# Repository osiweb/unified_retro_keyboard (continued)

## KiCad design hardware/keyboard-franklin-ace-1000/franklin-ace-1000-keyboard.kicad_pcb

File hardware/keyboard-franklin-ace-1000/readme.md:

# Franklin-ACE-1000-Keyboard
Replacement Franklin ACE 1000 keyboard for use with osiweb's Unified Retro Keyboard

## Images

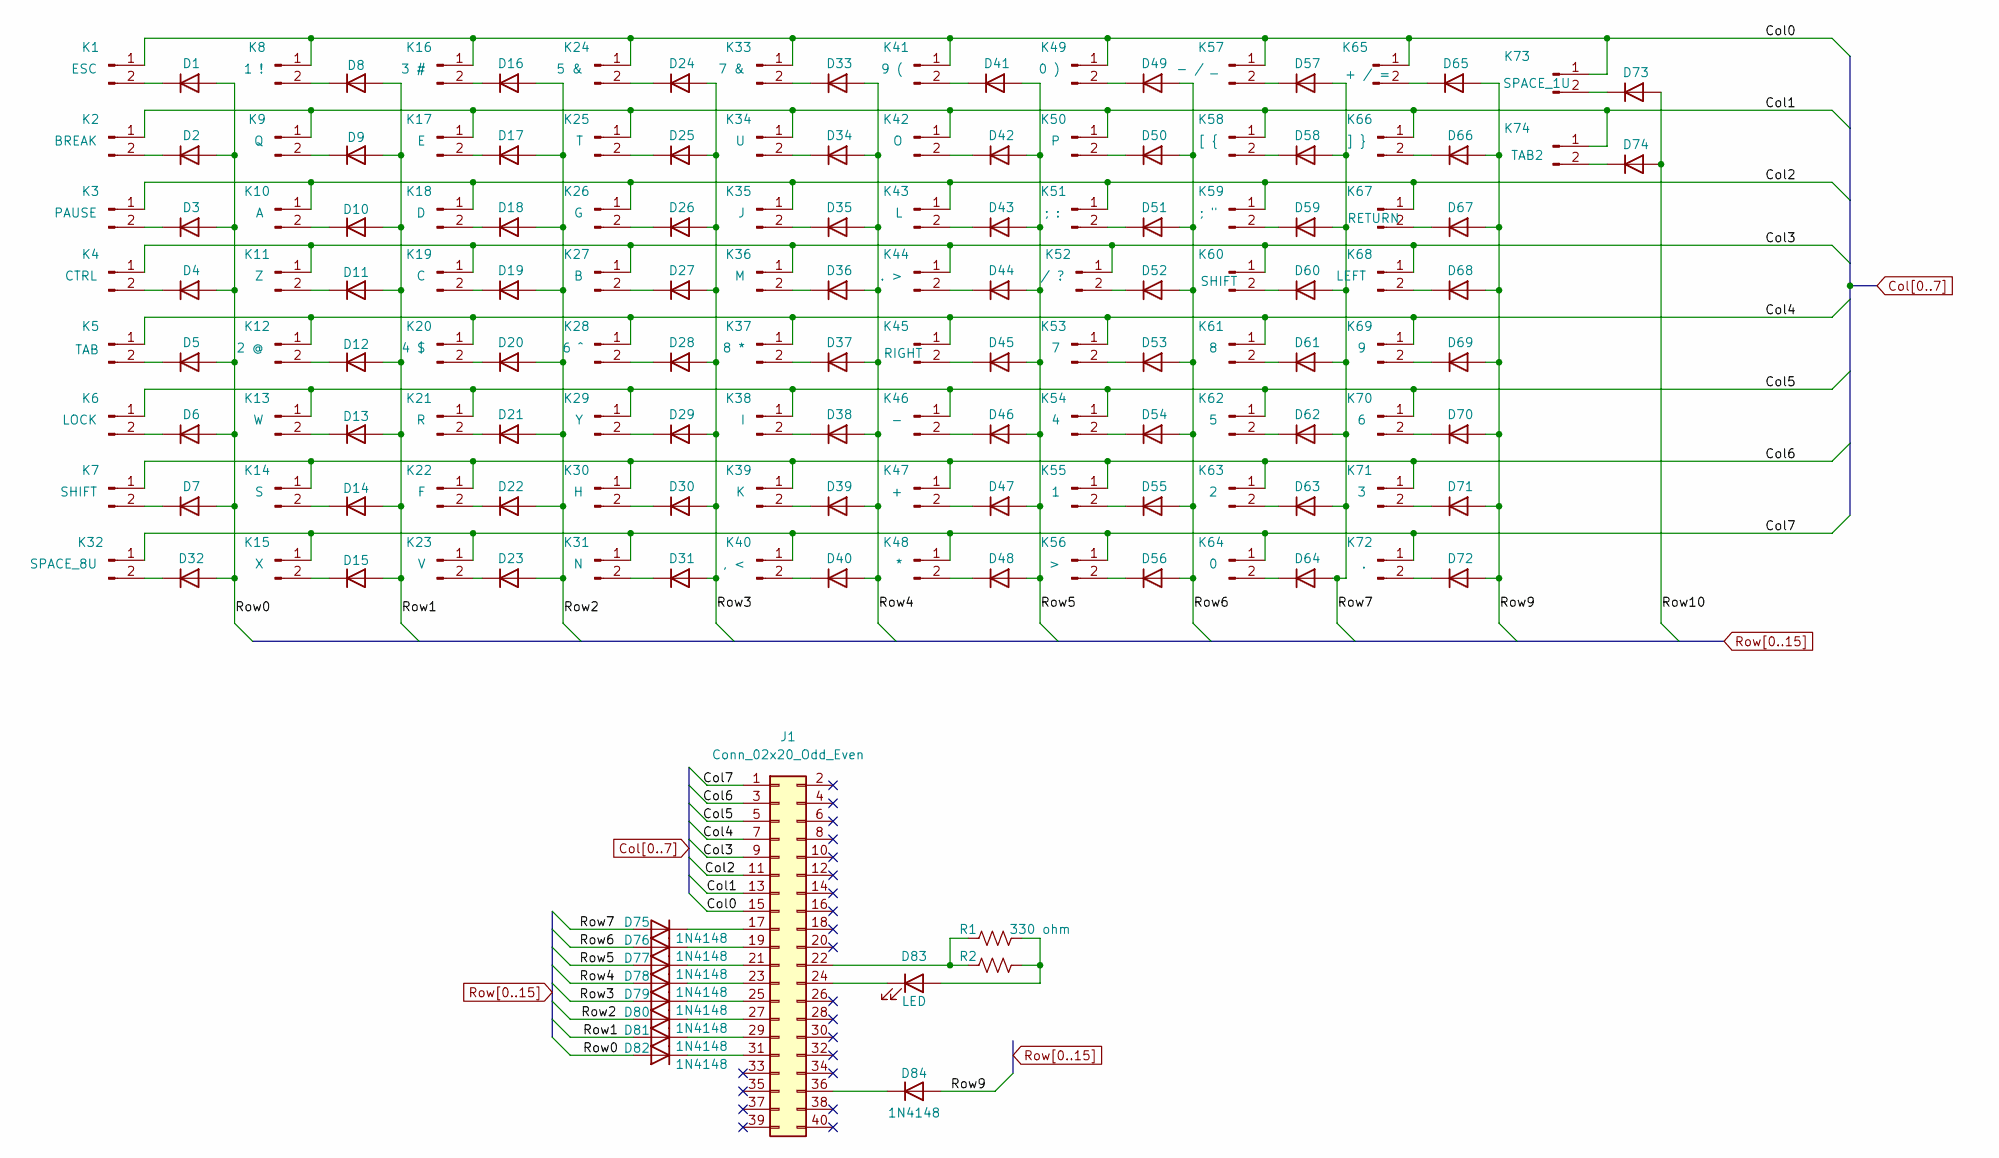
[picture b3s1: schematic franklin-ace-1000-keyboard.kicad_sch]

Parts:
D1, D2, D3, D4, D5, D6, D7, D8, D9, D10, D11, D12, D13, D14, D15, D16, D17, D18, D19, D20, D21, D22, D23, D24, D25, D26, D27, D28, D29, D30, D31, D32, D33, D34, D35, D36, D37, D38, D39, D40, D41, D42, D43, D44, D45, D46, D47, D48, D49, D50, D51, D52, D53, D54, D55, D56, D57, D58, D59, D60, D61, D62, D63, D64, D65, D66, D67, D68, D69, D70, D71, D72, D73, D74: diode-combined
D75, D76, D77, D78, D79, D80, D81, D82, D84: 1N4148; diode-combined
D83: LED; LED_D3.0mm
J1: Conn_02x20_Odd_Even; PinHeader_2x20_P2.54mm_Vertical
K1: ESC; Key_MX
K2: BREAK; Key_MX
K3: PAUSE; Key_MX
K4: CTRL; Key_MX
K5: TAB; Key_MX
K6: LOCK; Key_MX
K7, K60: SHIFT; Key_MX_2u
K8: 1 !; Key_MX
K9: Q; Key_MX
K10: A; Key_MX
K11: Z; Key_MX
K12: 2 @; Key_MX
K13: W; Key_MX
K14: S; Key_MX
K15: X; Key_MX
K16: 3 #; Key_MX
K17: E; Key_MX
K18: D; Key_MX
K19: C; Key_MX
K20: 4 $; Key_MX
K21: R; Key_MX
K22: F; Key_MX
K23: V; Key_MX
K24: 5 &; Key_MX
K25: T; Key_MX
K26: G; Key_MX
K27: B; Key_MX
K28: 6 ^; Key_MX
K29: Y; Key_MX
K30: H; Key_MX
K31: N; Key_MX
K32: SPACE_8U; Key_MX_Spacebar_5.25
K33: 7 &; Key_MX
K34: U; Key_MX
K35: J; Key_MX
K36: M; Key_MX
K37: 8 *; Key_MX
K38: I; Key_MX
K39: K; Key_MX
K40: , <; Key_MX
K41: 9 (; Key_MX
K42: O; Key_MX
K43: L; Key_MX
K44: . >; Key_MX
K45: RIGHT; Key_MX
K46: -; Key_MX
K47: +; Key_MX
K48: *; Key_MX
K49: 0 ); Key_MX
K50: P; Key_MX
K51: ; :; Key_MX
K52: / ?; Key_MX
K53: 7; Key_MX
K54: 4; Key_MX
K55: 1; Key_MX
K56: >; Key_MX
K57: - / _; Key_MX
K58: [ {; Key_MX
K59: ; "; Key_MX
K61: 8; Key_MX
K62: 5; Key_MX
K63: 2; Key_MX
K64: 0; Key_MX
K65: + / =; Key_MX
K66: ] }; Key_MX
K67: RETURN; Key_MX
K68: LEFT; Key_MX
K69: 9; Key_MX
K70: 6; Key_MX
K71: 3; Key_MX
K72: .; Key_MX
K73: SPACE_1U; Key_MX
K74: TAB2; Key_MX
R1: 330 ohms; R_Axial_DIN0207_L6.3mm_D2.5mm_P7.62mm_Horizontal; Tolerance 1%; Power Rating 1/4 W; Manufacturer PN MFR-25FTE52-330R
R2: RES 330 ohm 1% MLCC 0805 Yageo; R_0805_2012Metric; Tolerance 1%; Power Rating 125 mW; Manufacturer PN RC0805FR-07330RL

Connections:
Col0: J1.15, K1.1, K8.1, K16.1, K24.1, K33.1, K41.1, K49.1, K57.1, K65.1, K73.1
Col1: J1.13, K2.1, K9.1, K17.1, K25.1, K34.1, K42.1, K50.1, K58.1, K66.1, K74.1
Col2: J1.11, K3.1, K10.1, K18.1, K26.1, K35.1, K43.1, K51.1, K59.1, K67.1
Col3: J1.9, K4.1, K11.1, K19.1, K27.1, K36.1, K44.1, K52.1, K60.1, K68.1
Col4: J1.7, K5.1, K12.1, K20.1, K28.1, K37.1, K45.1, K53.1, K61.1, K69.1
Col5: J1.5, K6.1, K13.1, K21.1, K29.1, K38.1, K46.1, K54.1, K62.1, K70.1
Col6: J1.3, K7.1, K14.1, K22.1, K30.1, K39.1, K47.1, K55.1, K63.1, K71.1
Col7: J1.1, K15.1, K23.1, K31.1, K32.1, K40.1, K48.1, K56.1, K64.1, K72.1
unnamed: D1.1 (K), K1.2
unnamed: D2.1 (K), K2.2
unnamed: D3.1 (K), K3.2
unnamed: D4.1 (K), K4.2
unnamed: D5.1 (K), K5.2
unnamed: D6.1 (K), K6.2
unnamed: D7.1 (K), K7.2
unnamed: D8.1 (K), K8.2
unnamed: D9.1 (K), K9.2
unnamed: D10.1 (K), K10.2
unnamed: D11.1 (K), K11.2
unnamed: D12.1 (K), K12.2
unnamed: D13.1 (K), K13.2
unnamed: D14.1 (K), K14.2
unnamed: D15.1 (K), K15.2
unnamed: D16.1 (K), K16.2
unnamed: D17.1 (K), K17.2
unnamed: D18.1 (K), K18.2
unnamed: D19.1 (K), K19.2
unnamed: D20.1 (K), K20.2
unnamed: D21.1 (K), K21.2
unnamed: D22.1 (K), K22.2
unnamed: D23.1 (K), K23.2
unnamed: D24.1 (K), K24.2
unnamed: D25.1 (K), K25.2
unnamed: D26.1 (K), K26.2
unnamed: D27.1 (K), K27.2
unnamed: D28.1 (K), K28.2
unnamed: D29.1 (K), K29.2
unnamed: D30.1 (K), K30.2
unnamed: D31.1 (K), K31.2
unnamed: D32.1 (K), K32.2
unnamed: D33.1 (K), K33.2
unnamed: D34.1 (K), K34.2
unnamed: D35.1 (K), K35.2
unnamed: D36.1 (K), K36.2
unnamed: D37.1 (K), K37.2
unnamed: D38.1 (K), K38.2
unnamed: D39.1 (K), K39.2
unnamed: D40.1 (K), K40.2
unnamed: D41.1 (K), K41.2
unnamed: D42.1 (K), K42.2
unnamed: D43.1 (K), K43.2
unnamed: D44.1 (K), K44.2
unnamed: D45.1 (K), K45.2
unnamed: D46.1 (K), K46.2
unnamed: D47.1 (K), K47.2
unnamed: D48.1 (K), K48.2
unnamed: D49.1 (K), K49.2
unnamed: D50.1 (K), K50.2
unnamed: D51.1 (K), K51.2
unnamed: D52.1 (K), K52.2
unnamed: D53.1 (K), K53.2
unnamed: D54.1 (K), K54.2
unnamed: D55.1 (K), K55.2
unnamed: D56.1 (K), K56.2
unnamed: D57.1 (K), K57.2
unnamed: D58.1 (K), K58.2
unnamed: D59.1 (K), K59.2
unnamed: D60.1 (K), K60.2
unnamed: D61.1 (K), K61.2
unnamed: D62.1 (K), K62.2
unnamed: D63.1 (K), K63.2
unnamed: D64.1 (K), K64.2
unnamed: D65.1 (K), K65.2
unnamed: D66.1 (K), K66.2
unnamed: D67.1 (K), K67.2
unnamed: D68.1 (K), K68.2
unnamed: D69.1 (K), K69.2
unnamed: D70.1 (K), K70.2
unnamed: D71.1 (K), K71.2
unnamed: D72.1 (K), K72.2
unnamed: D73.1 (K), K73.2
unnamed: D74.1 (K), K74.2
unnamed: D75.1 (K), J1.17
unnamed: D76.1 (K), J1.19
unnamed: D77.1 (K), J1.21
unnamed: D78.1 (K), J1.23
unnamed: D79.1 (K), J1.25
unnamed: D80.1 (K), J1.27
unnamed: D81.1 (K), J1.29
unnamed: D82.1 (K), J1.31
unnamed: D83.2 (A), R1.1, R2.1
unnamed: D83.1 (K), J1.24
unnamed: D84.1 (K), J1.36
unnamed: J1.22, R1.2, R2.2
Row0: D1.2 (A), D2.2 (A), D3.2 (A), D4.2 (A), D5.2 (A), D6.2 (A), D7.2 (A), D32.2 (A), D82.2 (A)
Row1: D8.2 (A), D9.2 (A), D10.2 (A), D11.2 (A), D12.2 (A), D13.2 (A), D14.2 (A), D15.2 (A), D81.2 (A)
Row2: D16.2 (A), D17.2 (A), D18.2 (A), D19.2 (A), D20.2 (A), D21.2 (A), D22.2 (A), D23.2 (A), D80.2 (A)
Row3: D24.2 (A), D25.2 (A), D26.2 (A), D27.2 (A), D28.2 (A), D29.2 (A), D30.2 (A), D31.2 (A), D79.2 (A)
Row4: D33.2 (A), D34.2 (A), D35.2 (A), D36.2 (A), D37.2 (A), D38.2 (A), D39.2 (A), D40.2 (A), D78.2 (A)
Row5: D41.2 (A), D42.2 (A), D43.2 (A), D44.2 (A), D45.2 (A), D46.2 (A), D47.2 (A), D48.2 (A), D77.2 (A)
Row6: D49.2 (A), D50.2 (A), D51.2 (A), D52.2 (A), D53.2 (A), D54.2 (A), D55.2 (A), D56.2 (A), D76.2 (A)
Row7: D57.2 (A), D58.2 (A), D59.2 (A), D60.2 (A), D61.2 (A), D62.2 (A), D63.2 (A), D64.2 (A), D75.2 (A)
Row9: D65.2 (A), D66.2 (A), D67.2 (A), D68.2 (A), D69.2 (A), D70.2 (A), D71.2 (A), D72.2 (A), D84.2 (A)
Row10: D73.2 (A), D74.2 (A)

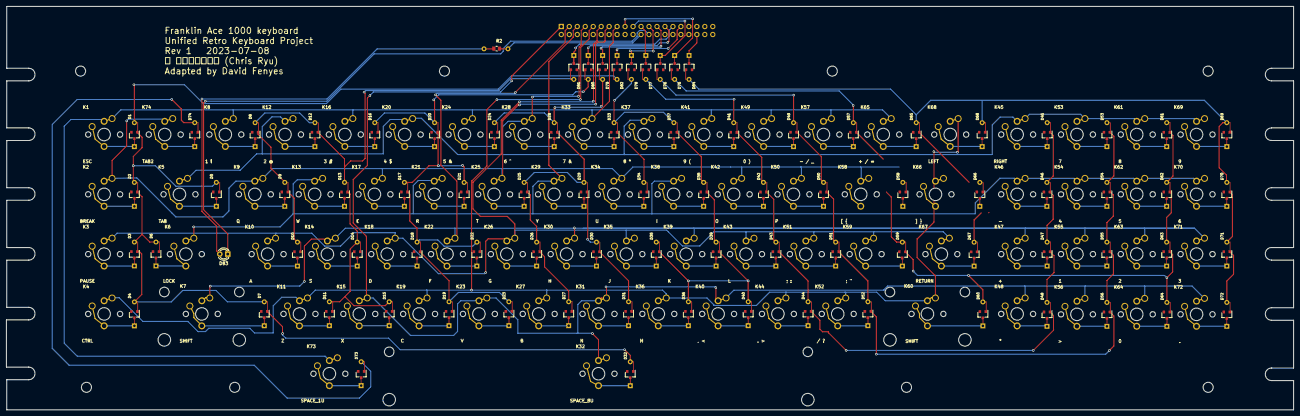
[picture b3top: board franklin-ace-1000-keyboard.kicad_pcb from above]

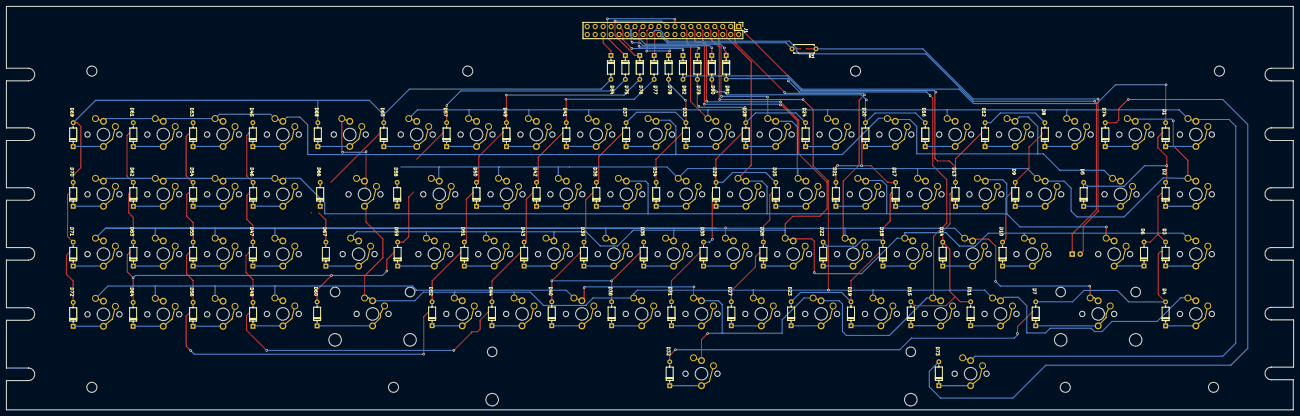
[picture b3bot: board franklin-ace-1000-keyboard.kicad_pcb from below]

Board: 2 copper layers, 410.0 x 128.5 mm, 161 parts (2 on the bottom side), 104 nets.

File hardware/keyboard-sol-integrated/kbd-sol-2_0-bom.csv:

Comment,Designator,Footprint,LCSC
36pf,"C1,C2",Capacitor_SMD:C_0603_1608Metric,C134070
0.1 uF,"C3,C4,C5,C6,C7",Capacitor_SMD:C_0603_1608Metric,C14663
1N4148,"D1,D2,D3,D4,D5,D6,D7,D8,D9,D10,D11,D12,D13,D14,D15,D16,D17,D18,D19,D20,D21,D22,D23,D24,D25,D26,D27,D28,D29,D30,D31,D32,D33,D34,D35,D36,D37,D38,D39,D40,D41,D42,D43,D44,D45,D46,D47,D48,D49,D50,D51,D52,D53,D54,D55,D56,D57,D58,D59,D60,D61,D62,D63,D64,D65,D66,D67,D68,D69,D70,D71,D72,D73,D74,D75,D76,D77,D78,D79,D80,D81,D82,D83,D84,D85, D86,D87,D88,D89,D90,D91,D92,D93",unikbd:diode-combined,C118751
330,"R4,R5,R6",Resistor_SMD:R_0805_2012Metric,
10k,R7,Resistor_SMD:R_0603_1608Metric,C98220
ATmega2560-16AU,U1,Package_QFP:TQFP-100_14x14mm_P0.5mm,C22460
16.000 MHz,Y1,Crystal:Crystal_SMD_HC49-SD,C326544

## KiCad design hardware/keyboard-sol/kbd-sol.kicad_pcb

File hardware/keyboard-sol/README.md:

# SOL keyboard

This keyboard replicates the keyboard on the SOL-20.

This keyboad matrix works with one of the add-on ASCII encoders from this
project, which must be separately built or acquired.

This keyboard has a sibling Sol-20 keyboard with integrated
encoder [(here)](../keyboard-sol-integrated). The two keyboards are identical except for the following difference:

1. The integrated version places the connector closer to the main board keyboard
   socket, so the original cable fits more easily.

1. This non-integrated version requires a piggy-back encoder board. When
   installing in a Sol-20, this piggyback board must be mounted on the right
   side of the keyboard, and connected with a cable, to avoid mechanical
   interference from the Sol main board.
   
1. The piggy-back encoder permits use with other machines, via the Apple-1 and
   Apple-2 sockets, and two different user-configurable headers.
   
1. The piggy-back encoder also includes a UART interface.

The keyboard is designed using KiCad in order to be the most useful for anybody
wishing to modify the keyboard for more specific uses, or to add to the project.

The keyset for the SOL-20 keyboard consists of the Unified Keyboard Project
classic ASCII keyset, with a special SOL-20 add-on keyset.

## Differences from the original include:

1. The original keyboard is a capacitive keyboard. This keyboard uses standard
   switches (either Cherry or Futaba).
   
1. The original keycaps have an 11 degree angled stem. It may be possible to
   find such keycaps, but I was unable to find any. It also may be possible to
   create 11 degree adapters. But this keyboard uses straight keycaps. I have
   tried both styles, and do not find a difference in typing comfort or speed,
   althought there is an aesthetic difference. There is s tiny bit of space
   between keys using straight keycaps, so an 11 degree adapter may not require
   any change to the layout.

1. The original uses UPPERCASE+REPEAT to reset the system. For technical
   reasons, this version uses CTRL+MODE_SELECT to RESET the system.

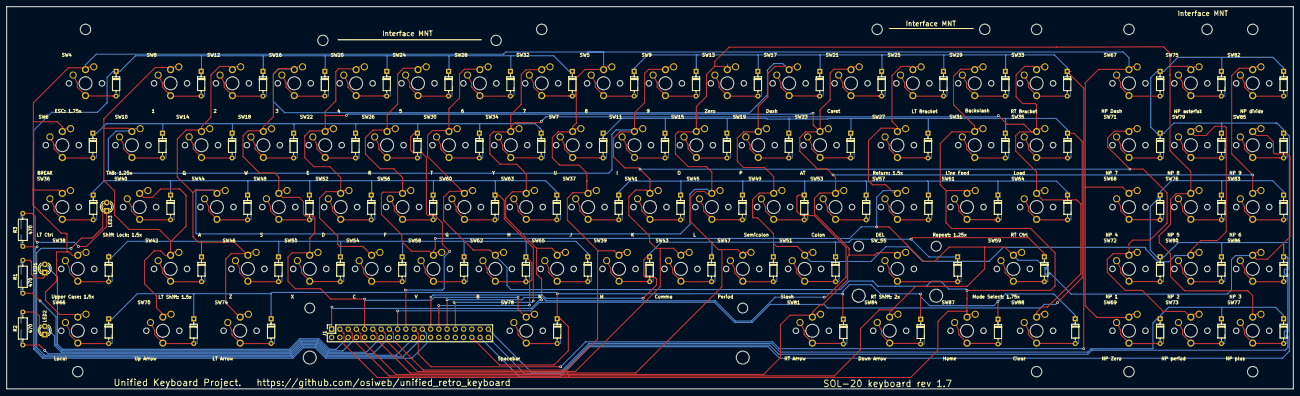
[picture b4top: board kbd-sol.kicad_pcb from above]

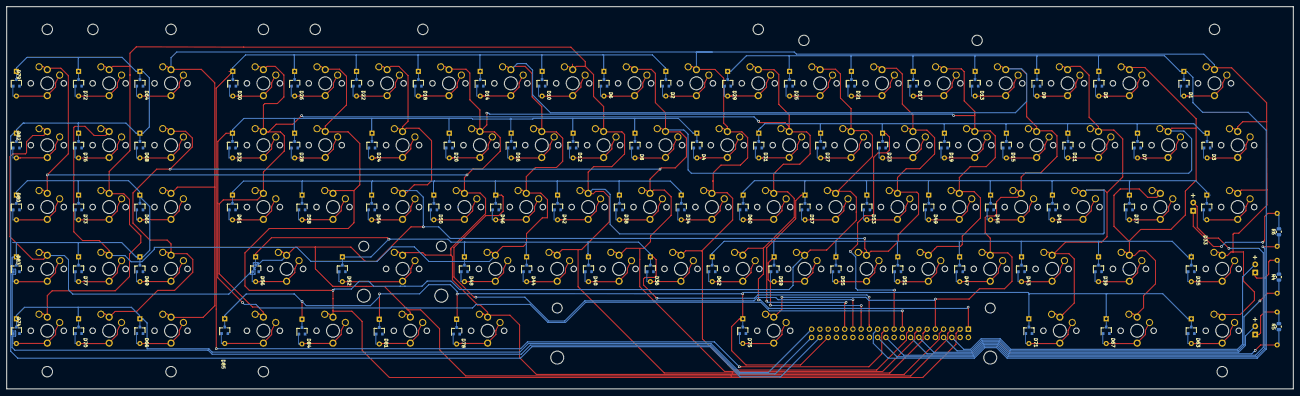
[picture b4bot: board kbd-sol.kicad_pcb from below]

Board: 2 copper layers, 396.2 x 117.7 mm, 180 parts (88 on the bottom side), 114 nets.

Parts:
D1, D2, D3, D4, D5, D6, D7, D8, D9, D10, D11, D12, D13, D14, D15, D16, D17, D18, D19, D20, D21, D22, D23, D24, D25, D26, D27, D28, D29, D30, D31, D32, D33, D34, D35, D36, D37, D38, D39, D40, D41, D42, D43, D44, D45, D46, D47, D48, D49, D50, D51, D52, D53, D54, D55, D56, D57, D58, D59, D60, D61, D62, D63, D64, D65, D66, D67, D68, D69, D70, D71, D72, D73, D74, D75, D76, D77, D78, D79, D80, D81, D82, D83, D84, D85: 1N4148; diode-combined
J1: Controller; kbd_header_two_mounting_holes
LED1, LED2, LED3: LED; LED_D3.0mm
R1, R2, R3: 470; R_Axial_DIN0207_L6.3mm_D2.5mm_P10.16mm_Horizontal
R4, R5, R6: 470; R_0805_2012Metric
SW4: ESC: 1.75x; Key_MX
SW5: 8; Key_MX
SW6: BREAK; Key_MX
SW7: U; Key_MX
SW8: 1; Key_MX
SW9: 9; Key_MX
SW10: TAB: 1.25x; Key_MX
SW11: I; Key_MX
SW12: 2; Key_MX
SW13: Zero; Key_MX
SW14: Q; Key_MX
SW15: O; Key_MX
SW16: 3; Key_MX
SW17: Dash; Key_MX
SW18: W; Key_MX
SW19: P; Key_MX
SW20: 4; Key_MX
SW21: Caret; Key_MX
SW22: E; Key_MX
SW23: AT; Key_MX
SW24: 5; Key_MX
SW25: LT Bracket; Key_MX
SW26: R; Key_MX
SW27: Return: 1.5x; Key_MX
SW28: 6; Key_MX
SW29: Backslash; Key_MX
SW30: T; Key_MX
SW31: Line Feed; Key_MX
SW32: 7; Key_MX
SW33: RT Bracket; Key_MX
SW34: Y; Key_MX
SW35: Load; Key_MX
SW36: LT Ctrl; Key_MX
SW37: J; Key_MX
SW38: Upper Case: 1.5x; Key_MX
SW39: M; Key_MX
SW40: Shift Lock: 1.5x; Key_MX
SW41: K; Key_MX
SW42: LT Shift: 1.5x; Key_MX
SW43: Comma; Key_MX
SW44: A; Key_MX
SW45: L; Key_MX
SW46: Z; Key_MX
SW47: Period; Key_MX
SW48: S; Key_MX
SW49: Semicolon; Key_MX
SW50: X; Key_MX
SW51: Slash; Key_MX
SW52: D; Key_MX
SW53: Colon; Key_MX
SW54: C; Key_MX
SW55: RT Shift: 2x; Key_MX_2u
SW56: F; Key_MX
SW57: DEL; Key_MX
SW58: V; Key_MX
SW59: Mode Select: 1.75x; Key_MX
SW60: G; Key_MX
SW61: Repeat: 1.25x; Key_MX
SW62: B; Key_MX
SW63: H; Key_MX
SW64: RT Ctrl; Key_MX
SW65: N; Key_MX
SW66: Local; Key_MX
SW67: NP Dash; Key_MX
SW68: NP 4; Key_MX
SW69: NP Zero; Key_MX
SW70: Up Arrow; Key_MX
SW71: NP 7; Key_MX
SW72: NP 1; Key_MX
SW73: NP period; Key_MX
SW74: LT Arrow; Key_MX
SW75: NP asterisk; Key_MX
SW76: NP 5; Key_MX
SW77: NP plus; Key_MX
SW78: Spacebar; Key_MX_Spacebar_5.25
SW79: NP 8; Key_MX
SW80: NP 2; Key_MX
SW81: RT Arrow; Key_MX
SW82: NP divide; Key_MX
SW83: NP 6; Key_MX
SW84: Down Arrow; Key_MX
SW85: NP 9; Key_MX
SW86: NP 3; Key_MX
SW87: Home; Key_MX
SW88: Clear; Key_MX

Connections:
/Col0: J1.15, SW4.1, SW5.1, SW6.1, SW7.1, SW36.1, SW37.1, SW38.1, SW39.1, SW66.1, SW67.1, SW68.1, SW69.1
/Col1: J1.13, SW8.1, SW9.1, SW10.1, SW11.1, SW40.1, SW41.1, SW42.1, SW43.1, SW70.1, SW71.1, SW72.1, SW73.1
/Col2: J1.11, SW12.1, SW13.1, SW14.1, SW15.1, SW44.1, SW45.1, SW46.1, SW47.1, SW74.1, SW75.1, SW76.1, SW77.1
/Col3: J1.9, SW16.1, SW17.1, SW18.1, SW19.1, SW48.1, SW49.1, SW50.1, SW51.1, SW78.1, SW79.1, SW80.1
/Col4: J1.7, SW20.1, SW21.1, SW22.1, SW23.1, SW52.1, SW53.1, SW54.1, SW55.1, SW81.1, SW82.1, SW83.1
/Col5: J1.5, SW24.1, SW25.1, SW26.1, SW27.1, SW56.1, SW57.1, SW58.1, SW59.1, SW84.1, SW85.1, SW86.1
/Col6: J1.3, SW28.1, SW29.1, SW30.1, SW31.1, SW60.1, SW61.1, SW62.1, SW87.1
/Col7: J1.1, SW32.1, SW33.1, SW34.1, SW35.1, SW63.1, SW64.1, SW65.1, SW88.1
/Row0: D33.1, D37.1, D41.1, D45.1, D49.1, D53.1, D57.1, D60.1, J1.31
/Row1: D34.1, D38.1, D42.1, D46.1, D50.1, D54.1, D58.1, D61.1, J1.29
/Row2: D35.1, D39.1, D43.1, D47.1, D51.1, D55.1, D59.1, D62.1, J1.27
/Row3: D36.1, D40.1, D44.1, D48.1, D52.1, D56.1, J1.25
/Row4: D1.1, D5.1, D9.1, D13.1, D17.1, D21.1, D25.1, D29.1, J1.23
/Row5: D2.1, D6.1, D10.1, D14.1, D18.1, D22.1, D26.1, D30.1, J1.21
/Row6: D3.1, D7.1, D11.1, D15.1, D19.1, D23.1, D27.1, D31.1, J1.19
/Row7: D4.1, D8.1, D12.1, D16.1, D20.1, D24.1, D28.1, D32.1, J1.17
/Row9: D63.1, D67.1, D71.1, D75.1, D78.1, D81.1, D84.1, D85.1, J1.36
/Row10: D64.1, D68.1, D72.1, D76.1, D79.1, D82.1, J1.38
/Row11: D65.1, D69.1, D73.1, D77.1, D80.1, D83.1, J1.40
/Row12: D66.1, D70.1, D74.1, J1.39
unnamed: D1.2, SW4.2
unnamed: D2.2, SW5.2
unnamed: D3.2, SW6.2
unnamed: D4.2, SW7.2
unnamed: D5.2, SW8.2
unnamed: D6.2, SW9.2
unnamed: D7.2, SW10.2
unnamed: D8.2, SW11.2
unnamed: D9.2, SW12.2
unnamed: D10.2, SW13.2
unnamed: D11.2, SW14.2
unnamed: D12.2, SW15.2
unnamed: D13.2, SW16.2
unnamed: D14.2, SW17.2
unnamed: D15.2, SW18.2
unnamed: D16.2, SW19.2
unnamed: D17.2, SW20.2
unnamed: D18.2, SW21.2
unnamed: D19.2, SW22.2
unnamed: D20.2, SW23.2
unnamed: D21.2, SW24.2
unnamed: D22.2, SW25.2
unnamed: D23.2, SW26.2
unnamed: D24.2, SW27.2
unnamed: D25.2, SW28.2
unnamed: D26.2, SW29.2
unnamed: D27.2, SW30.2
unnamed: D28.2, SW31.2
unnamed: D29.2, SW32.2
unnamed: D30.2, SW33.2
unnamed: D31.2, SW34.2
unnamed: D32.2, SW35.2
unnamed: D33.2, SW36.2
unnamed: D34.2, SW37.2
unnamed: D35.2, SW38.2
unnamed: D36.2, SW39.2
unnamed: D37.2, SW40.2
unnamed: D38.2, SW41.2
unnamed: D39.2, SW42.2
unnamed: D40.2, SW43.2
unnamed: D41.2, SW44.2
unnamed: D42.2, SW45.2
unnamed: D43.2, SW46.2
unnamed: D44.2, SW47.2
unnamed: D45.2, SW48.2
unnamed: D46.2, SW49.2
unnamed: D47.2, SW50.2
unnamed: D48.2, SW51.2
unnamed: D49.2, SW52.2
unnamed: D50.2, SW53.2
unnamed: D51.2, SW54.2
unnamed: D52.2, SW55.2
unnamed: D53.2, SW56.2
unnamed: D54.2, SW57.2
unnamed: D55.2, SW58.2
unnamed: D56.2, SW59.2
unnamed: D57.2, SW60.2
unnamed: D58.2, SW61.2
unnamed: D59.2, SW62.2
unnamed: D60.2, SW63.2
unnamed: D61.2, SW64.2
unnamed: D62.2, SW65.2
unnamed: D63.2, SW66.2
unnamed: D64.2, SW67.2
unnamed: D65.2, SW68.2
unnamed: D66.2, SW69.2
unnamed: D67.2, SW70.2
unnamed: D68.2, SW71.2
unnamed: D69.2, SW72.2
unnamed: D70.2, SW73.2
unnamed: D71.2, SW74.2
unnamed: D72.2, SW75.2
unnamed: D73.2, SW76.2
unnamed: D74.2, SW77.2
unnamed: D75.2, SW78.2
unnamed: D76.2, SW79.2
unnamed: D77.2, SW80.2
unnamed: D78.2, SW81.2
unnamed: D79.2, SW82.2
unnamed: D80.2, SW83.2
unnamed: D81.2, SW84.2
unnamed: D82.2, SW85.2
unnamed: D83.2, SW86.2
unnamed: D84.2, SW87.2
unnamed: D85.2, SW88.2
unnamed: J1.6, LED1.2
unnamed: J1.8, R1.1, R4.1
unnamed: J1.14, LED2.2
unnamed: J1.16, R2.1, R5.1
unnamed: J1.22, LED3.2
unnamed: J1.24, R3.1, R6.1
unnamed: LED1.1, R1.2, R4.2
unnamed: LED2.1, R2.2, R5.2
unnamed: LED3.1, R3.2, R6.2

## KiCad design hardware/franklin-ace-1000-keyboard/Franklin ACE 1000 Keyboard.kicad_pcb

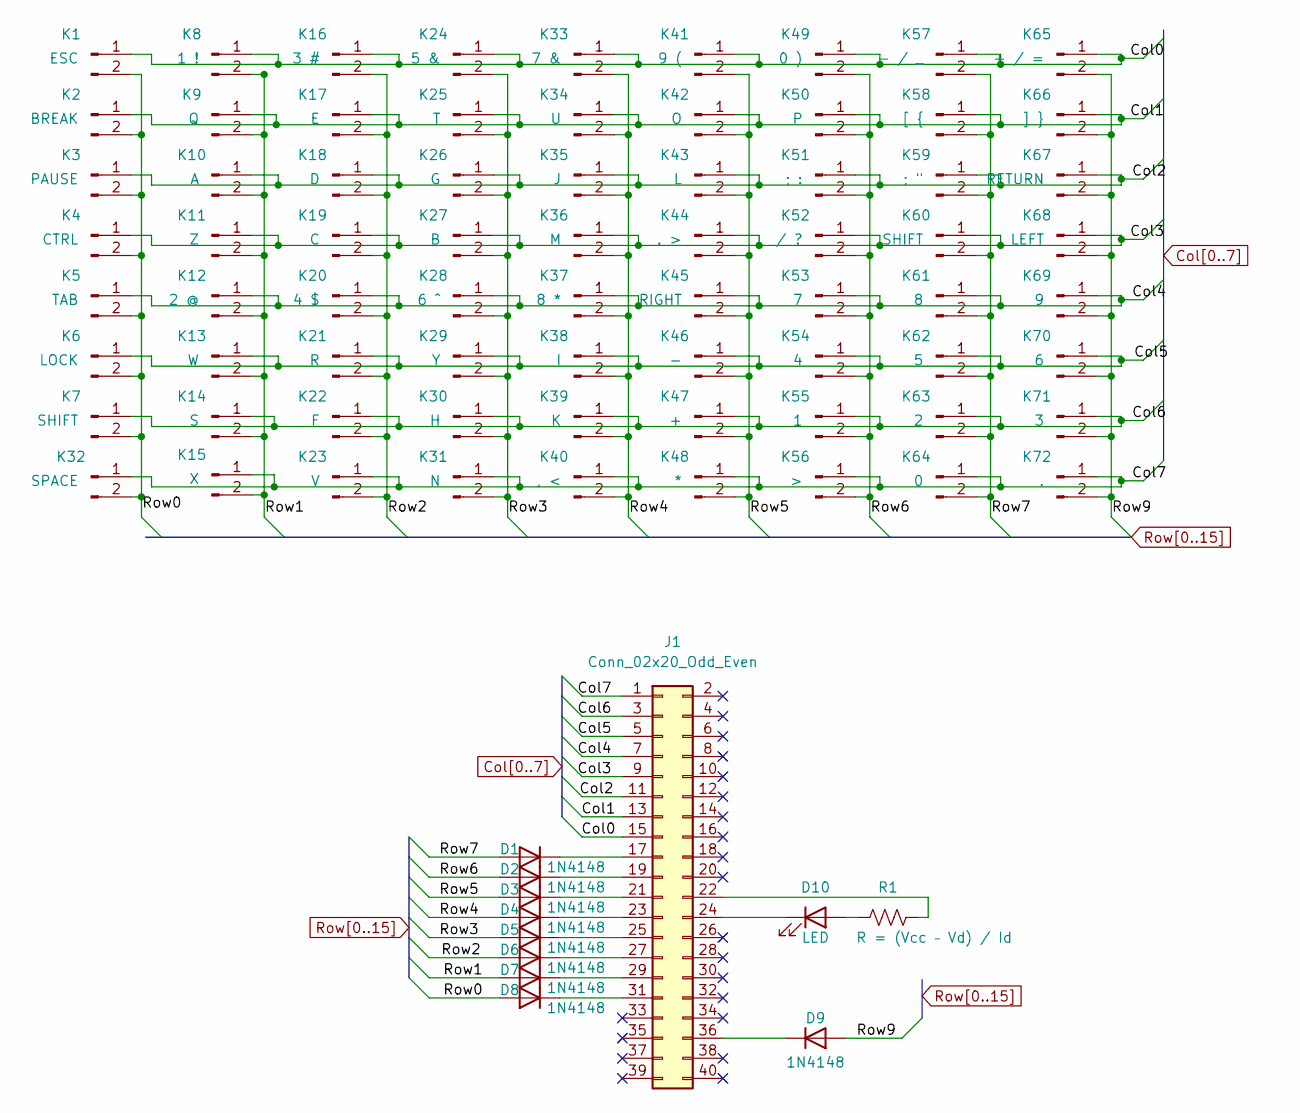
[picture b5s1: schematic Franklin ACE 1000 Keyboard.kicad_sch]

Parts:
D1, D2, D3, D4, D5, D6, D7, D8, D9: 1N4148; D_DO-35_SOD27_P7.62mm_Horizontal
D10: LED; LED_D3.0mm
J1: Conn_02x20_Odd_Even; PinHeader_2x20_P2.54mm_Vertical
K1: ESC; SW_Cherry_MX_1.00u_Plate
K2: BREAK; SW_Cherry_MX_1.00u_Plate
K3: PAUSE; SW_Cherry_MX_1.00u_Plate
K4: CTRL; SW_Cherry_MX_1.00u_Plate
K5: TAB; SW_Cherry_MX_1.50u_Plate
K6: LOCK; SW_Cherry_MX_1.00u_Plate
K7: SHIFT; SW_Cherry_MX_2.25u_Plate
K8: 1 !; SW_Cherry_MX_1.00u_Plate
K9: Q; SW_Cherry_MX_1.00u_Plate
K10: A; SW_Cherry_MX_1.00u_Plate
K11: Z; SW_Cherry_MX_1.00u_Plate
K12: 2 @; SW_Cherry_MX_1.00u_Plate
K13: W; SW_Cherry_MX_1.00u_Plate
K14: S; SW_Cherry_MX_1.00u_Plate
K15: X; SW_Cherry_MX_1.00u_Plate
K16: 3 #; SW_Cherry_MX_1.00u_Plate
K17: E; SW_Cherry_MX_1.00u_Plate
K18: D; SW_Cherry_MX_1.00u_Plate
K19: C; SW_Cherry_MX_1.00u_Plate
K20: 4 $; SW_Cherry_MX_1.00u_Plate
K21: R; SW_Cherry_MX_1.00u_Plate
K22: F; SW_Cherry_MX_1.00u_Plate
K23: V; SW_Cherry_MX_1.00u_Plate
K24: 5 &; SW_Cherry_MX_1.00u_Plate
K25: T; SW_Cherry_MX_1.00u_Plate
K26: G; SW_Cherry_MX_1.00u_Plate
K27: B; SW_Cherry_MX_1.00u_Plate
K28: 6 ^; SW_Cherry_MX_1.00u_Plate
K29: Y; SW_Cherry_MX_1.00u_Plate
K30: H; SW_Cherry_MX_1.00u_Plate
K31: N; SW_Cherry_MX_1.00u_Plate
K32: SPACE; SW_Cherry_MX_6.25u_PCB
K33: 7 &; SW_Cherry_MX_1.00u_Plate
K34: U; SW_Cherry_MX_1.00u_Plate
K35: J; SW_Cherry_MX_1.00u_Plate
K36: M; SW_Cherry_MX_1.00u_Plate
K37: 8 *; SW_Cherry_MX_1.00u_Plate
K38: I; SW_Cherry_MX_1.00u_Plate
K39: K; SW_Cherry_MX_1.00u_Plate
K40: , <; SW_Cherry_MX_1.00u_Plate
K41: 9 (; SW_Cherry_MX_1.00u_Plate
K42: O; SW_Cherry_MX_1.00u_Plate
K43: L; SW_Cherry_MX_1.00u_Plate
K44: . >; SW_Cherry_MX_1.00u_Plate
K45: RIGHT; SW_Cherry_MX_1.00u_Plate
K46: -; SW_Cherry_MX_1.00u_Plate
K47: +; SW_Cherry_MX_1.00u_Plate
K48: *; SW_Cherry_MX_1.00u_Plate
K49: 0 ); SW_Cherry_MX_1.00u_Plate
K50: P; SW_Cherry_MX_1.00u_Plate
K51: ; :; SW_Cherry_MX_1.00u_Plate
K52: / ?; SW_Cherry_MX_1.00u_Plate
K53: 7; SW_Cherry_MX_1.00u_Plate
K54: 4; SW_Cherry_MX_1.00u_Plate
K55: 1; SW_Cherry_MX_1.00u_Plate
K56: >; SW_Cherry_MX_1.00u_Plate
K57: - / _; SW_Cherry_MX_1.00u_Plate
K58: [ {; SW_Cherry_MX_1.00u_Plate
K59: ; "; SW_Cherry_MX_1.00u_Plate
K60: SHIFT; SW_Cherry_MX_2.00u_Plate
K61: 8; SW_Cherry_MX_1.00u_Plate
K62: 5; SW_Cherry_MX_1.00u_Plate
K63: 2; SW_Cherry_MX_1.00u_Plate
K64: 0; SW_Cherry_MX_1.00u_Plate
K65: + / =; SW_Cherry_MX_1.00u_Plate
K66: ] }; SW_Cherry_MX_1.00u_Plate
K67: RETURN; SW_Cherry_MX_1.50u_Plate
K68: LEFT; SW_Cherry_MX_1.25u_Plate
K69: 9; SW_Cherry_MX_1.00u_Plate
K70: 6; SW_Cherry_MX_1.00u_Plate
K71: 3; SW_Cherry_MX_1.00u_Plate
K72: .; SW_Cherry_MX_1.00u_Plate
R1: R = (Vcc – Vd) / Id; R_Axial_DIN0207_L6.3mm_D2.5mm_P7.62mm_Horizontal

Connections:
Col0: J1.15, K1.1, K8.1, K16.1, K24.1, K33.1, K41.1, K49.1, K57.1, K65.1
Col1: J1.13, K2.1, K9.1, K17.1, K25.1, K34.1, K42.1, K50.1, K58.1, K66.1
Col2: J1.11, K3.1, K10.1, K18.1, K26.1, K35.1, K43.1, K51.1, K59.1, K67.1
Col3: J1.9, K4.1, K11.1, K19.1, K27.1, K36.1, K44.1, K52.1, K60.1, K68.1
Col4: J1.7, K5.1, K12.1, K20.1, K28.1, K37.1, K45.1, K53.1, K61.1, K69.1
Col5: J1.5, K6.1, K13.1, K21.1, K29.1, K38.1, K46.1, K54.1, K62.1, K70.1
Col6: J1.3, K7.1, K14.1, K22.1, K30.1, K39.1, K47.1, K55.1, K63.1, K71.1
Col7: J1.1, K15.1, K23.1, K31.1, K32.1, K40.1, K48.1, K56.1, K64.1, K72.1
unnamed: D1.1 (K), J1.17
unnamed: D2.1 (K), J1.19
unnamed: D3.1 (K), J1.21
unnamed: D4.1 (K), J1.23
unnamed: D5.1 (K), J1.25
unnamed: D6.1 (K), J1.27
unnamed: D7.1 (K), J1.29
unnamed: D8.1 (K), J1.31
unnamed: D9.1 (K), J1.36
unnamed: D10.2 (A), R1.1
unnamed: D10.1 (K), J1.24
unnamed: J1.22, R1.2
Row0: D8.2 (A), K1.2, K2.2, K3.2, K4.2, K5.2, K6.2, K7.2, K32.2
Row1: D7.2 (A), K8.2, K9.2, K10.2, K11.2, K12.2, K13.2, K14.2, K15.2
Row2: D6.2 (A), K16.2, K17.2, K18.2, K19.2, K20.2, K21.2, K22.2, K23.2
Row3: D5.2 (A), K24.2, K25.2, K26.2, K27.2, K28.2, K29.2, K30.2, K31.2
Row4: D4.2 (A), K33.2, K34.2, K35.2, K36.2, K37.2, K38.2, K39.2, K40.2
Row5: D3.2 (A), K41.2, K42.2, K43.2, K44.2, K45.2, K46.2, K47.2, K48.2
Row6: D2.2 (A), K49.2, K50.2, K51.2, K52.2, K53.2, K54.2, K55.2, K56.2
Row7: D1.2 (A), K57.2, K58.2, K59.2, K60.2, K61.2, K62.2, K63.2, K64.2
Row9: D9.2 (A), K65.2, K66.2, K67.2, K68.2, K69.2, K70.2, K71.2, K72.2

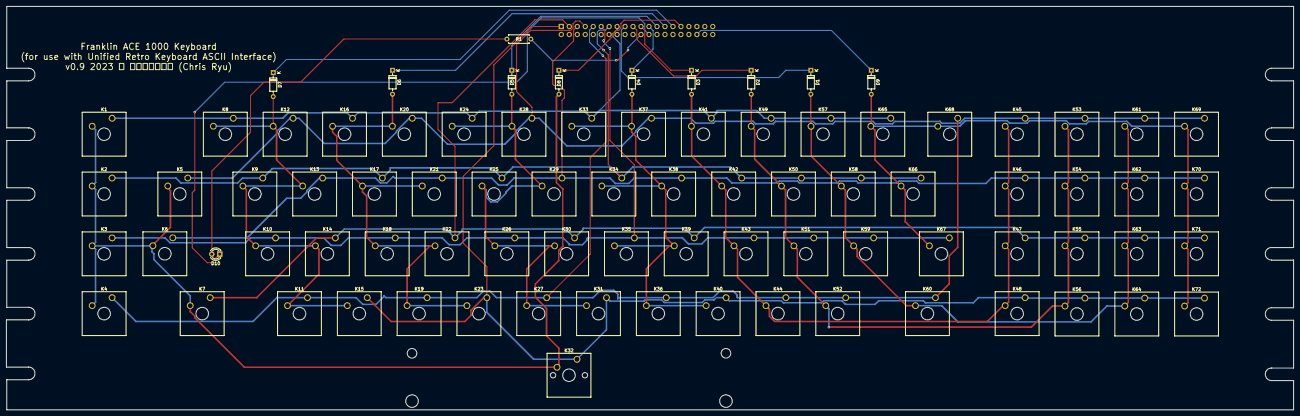
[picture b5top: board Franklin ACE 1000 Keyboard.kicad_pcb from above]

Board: 2 copper layers, 410.0 x 128.5 mm, 84 parts (1 on the bottom side), 29 nets.

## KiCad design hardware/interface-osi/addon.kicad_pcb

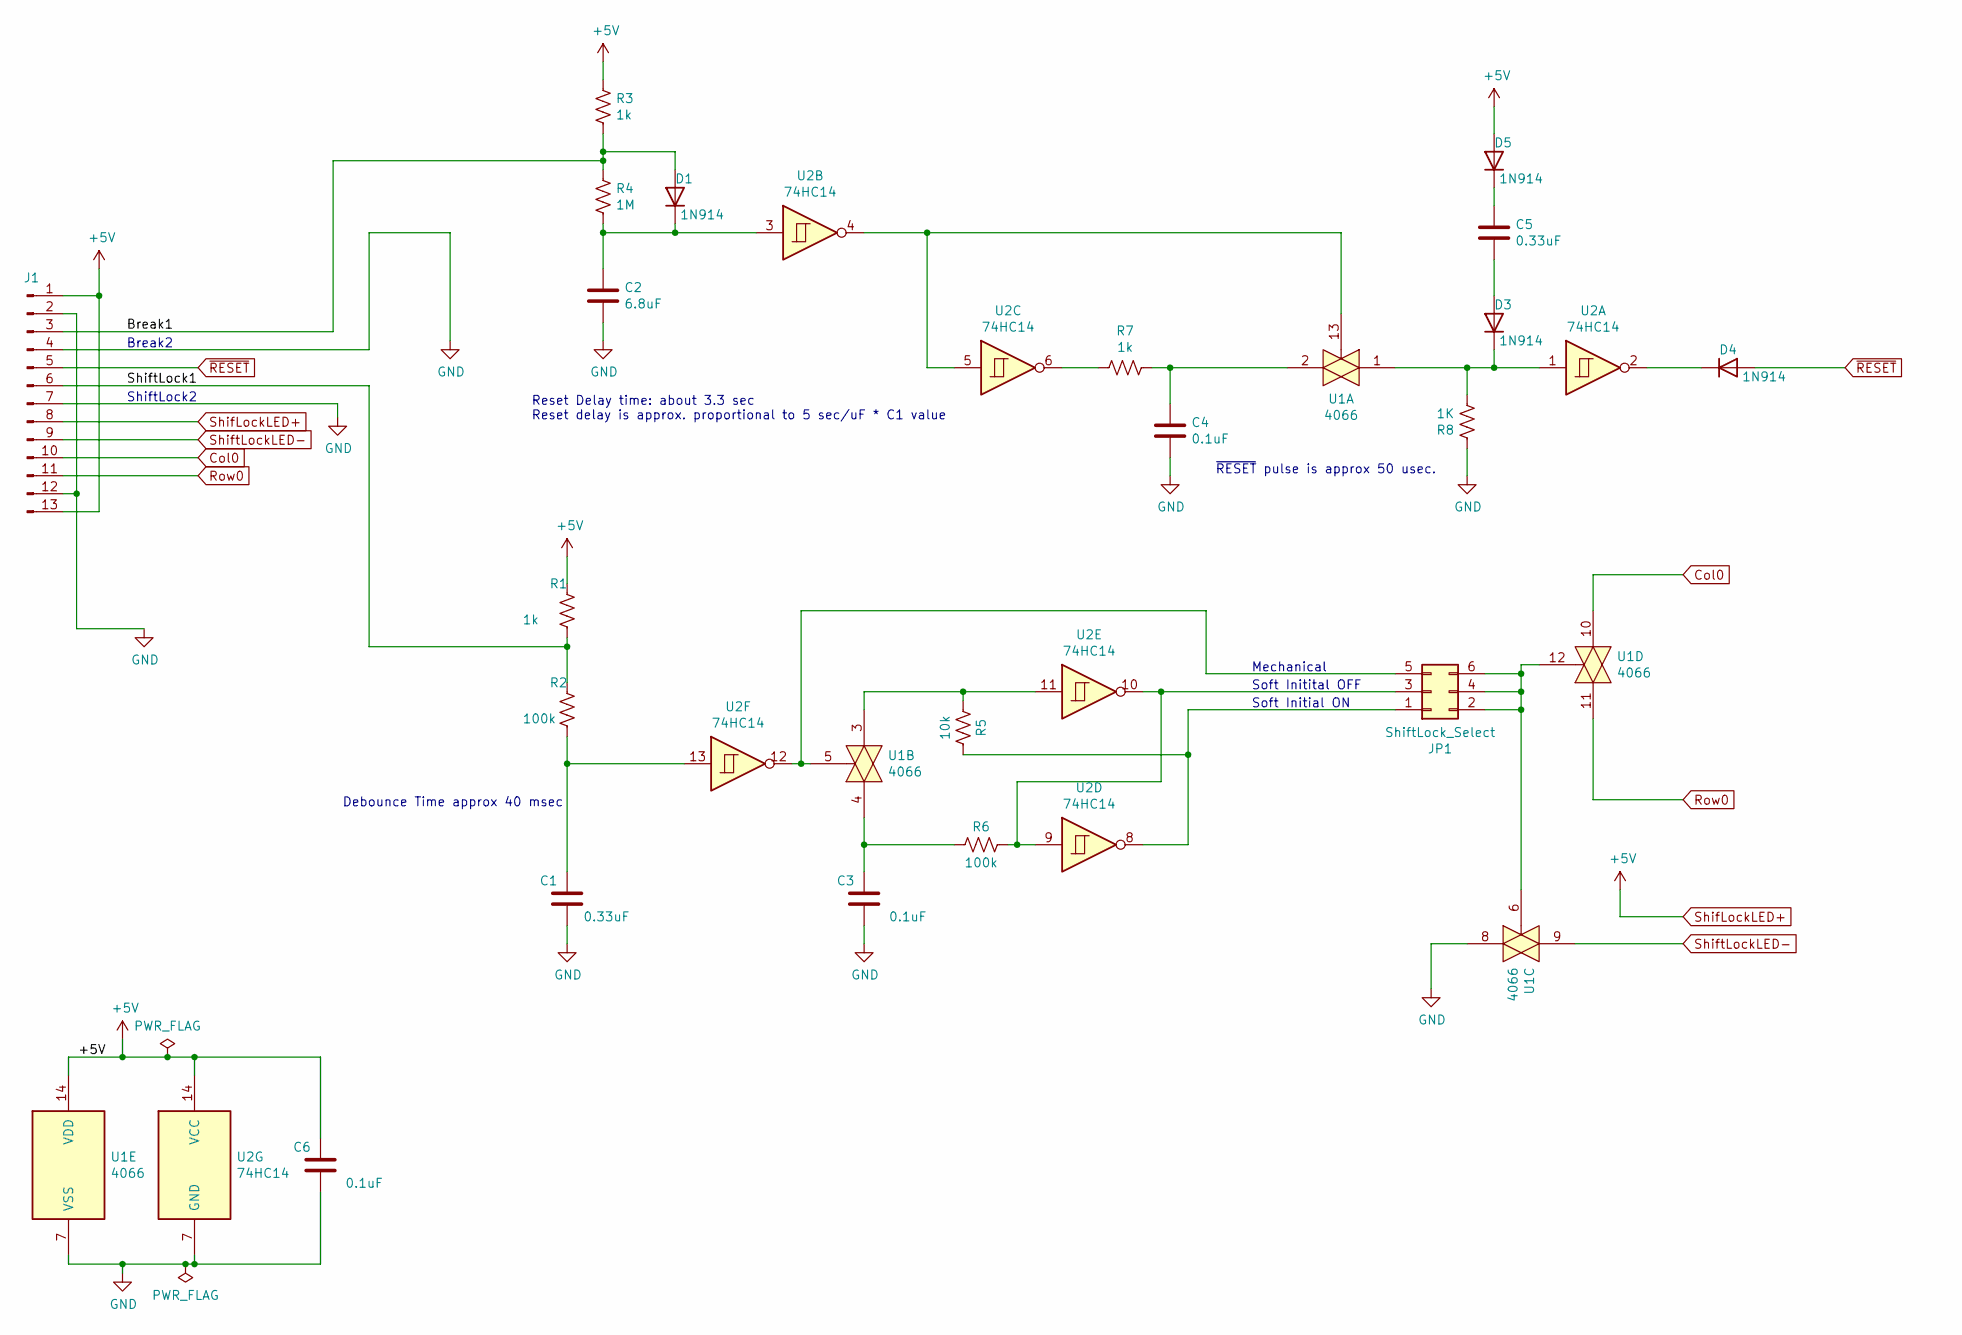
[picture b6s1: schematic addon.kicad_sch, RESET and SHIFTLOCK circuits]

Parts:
C1, C5: 0.33uF; C_Disc_D6.0mm_W2.5mm_P5.00mm
C2: 6.8uF; C_Disc_D6.0mm_W2.5mm_P5.00mm
C3, C4, C6: 0.1uF; C_Disc_D6.0mm_W2.5mm_P5.00mm
D1, D3, D4, D5: 1N914; D_DO-35_SOD27_P7.62mm_Horizontal
J1: Conn_01x13_Male; PinHeader_1x13_P2.54mm_Vertical
JP1: ShiftLock_Select; PinHeader_2x03_P2.54mm_Vertical
R1, R3, R7: 1k; R_Axial_DIN0207_L6.3mm_D2.5mm_P10.16mm_Horizontal
R2, R6: 100k; R_Axial_DIN0207_L6.3mm_D2.5mm_P10.16mm_Horizontal
R4: 1M; R_Axial_DIN0207_L6.3mm_D2.5mm_P10.16mm_Horizontal
R5: 10k; R_Axial_DIN0207_L6.3mm_D2.5mm_P10.16mm_Horizontal
R8: 1K; R_Axial_DIN0207_L6.3mm_D2.5mm_P10.16mm_Horizontal
U1: 4066; DIP-14_W7.62mm
U2: 74HC14; DIP-14_W7.62mm

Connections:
/Break1: D1.2 (A), J1.3, R3.2, R4.1
/ShiftLock1: J1.6, R1.2, R2.1
Col0: J1.10, U1.10
GND: C1.1, C2.2, C3.1, C4.2, C6.1, J1.2, J1.4, J1.7, J1.12, R8.1, U1.7 (VSS), U1.8, U2.7 (GND)
unnamed: C1.2, R2.2, U2.13
unnamed: C2.1, D1.1 (K), R4.2, U2.3
unnamed: C3.2, R6.1, U1.4
unnamed: C4.1, R7.1, U1.2
unnamed: C5.1, D5.1 (K)
unnamed: C5.2, D3.2 (A)
unnamed: D3.1 (K), R8.2, U1.1, U2.1
unnamed: D4.1 (K), U2.2
unnamed: JP1.1, R5.2, U2.8
unnamed: JP1.2, JP1.4, JP1.6, U1.6, U1.12
unnamed: JP1.3, R6.2, U2.9, U2.10
unnamed: JP1.5, U1.5, U2.12
unnamed: R5.1, U1.3, U2.11
unnamed: R7.2, U2.6
unnamed: U1.13, U2.4, U2.5
Row0: J1.11, U1.11
ShifLockLED+: C6.2, D5.2 (A), J1.1, J1.8, J1.13, R1.1, R3.1, U1.14 (VDD), U2.14 (VCC)
ShiftLockLED-: J1.9, U1.9
~RESET: D4.2 (A), J1.5

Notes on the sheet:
Mechanical
Soft Initital OFF
Break2
Reset Delay time: about 3.3 sec Reset delay is approx. proportional to 5 sec/uF * C1 value
Debounce Time approx 40 msec
~{RESET} pulse is approx 50 usec.
Soft Initial ON
ShiftLock2

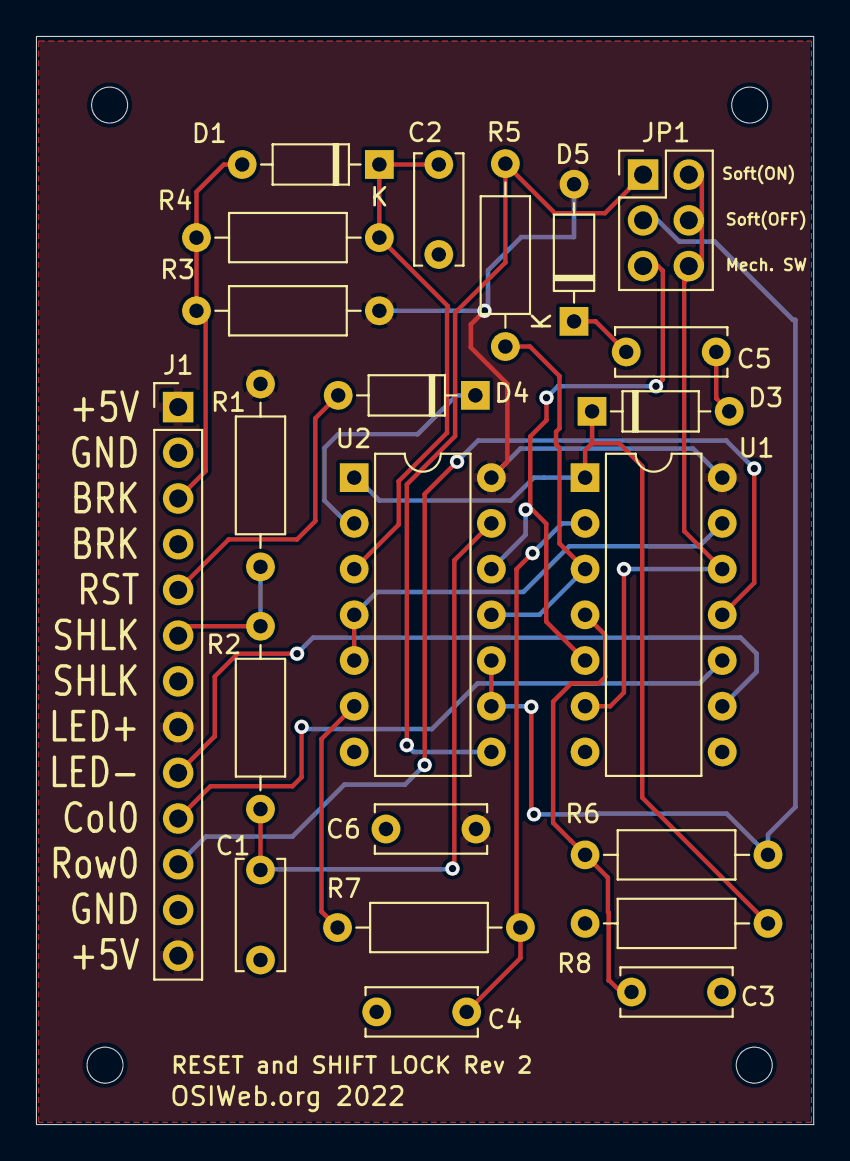
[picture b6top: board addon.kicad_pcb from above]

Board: 2 copper layers, 43.2 x 60.5 mm, 22 parts (0 on the bottom side), 23 nets.
